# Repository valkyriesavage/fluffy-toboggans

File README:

The Fluffy Toboggans : H2O IQ

A system for watering plants remotely: you don't have to worry about them!

Final presentation of this project : https://docs.google.com/presentation/d/1S5aFqThC5lc4pM-Y68lGRSMbOaRiJMXD9njBcWfeR2Q/edit

License: GPL v3

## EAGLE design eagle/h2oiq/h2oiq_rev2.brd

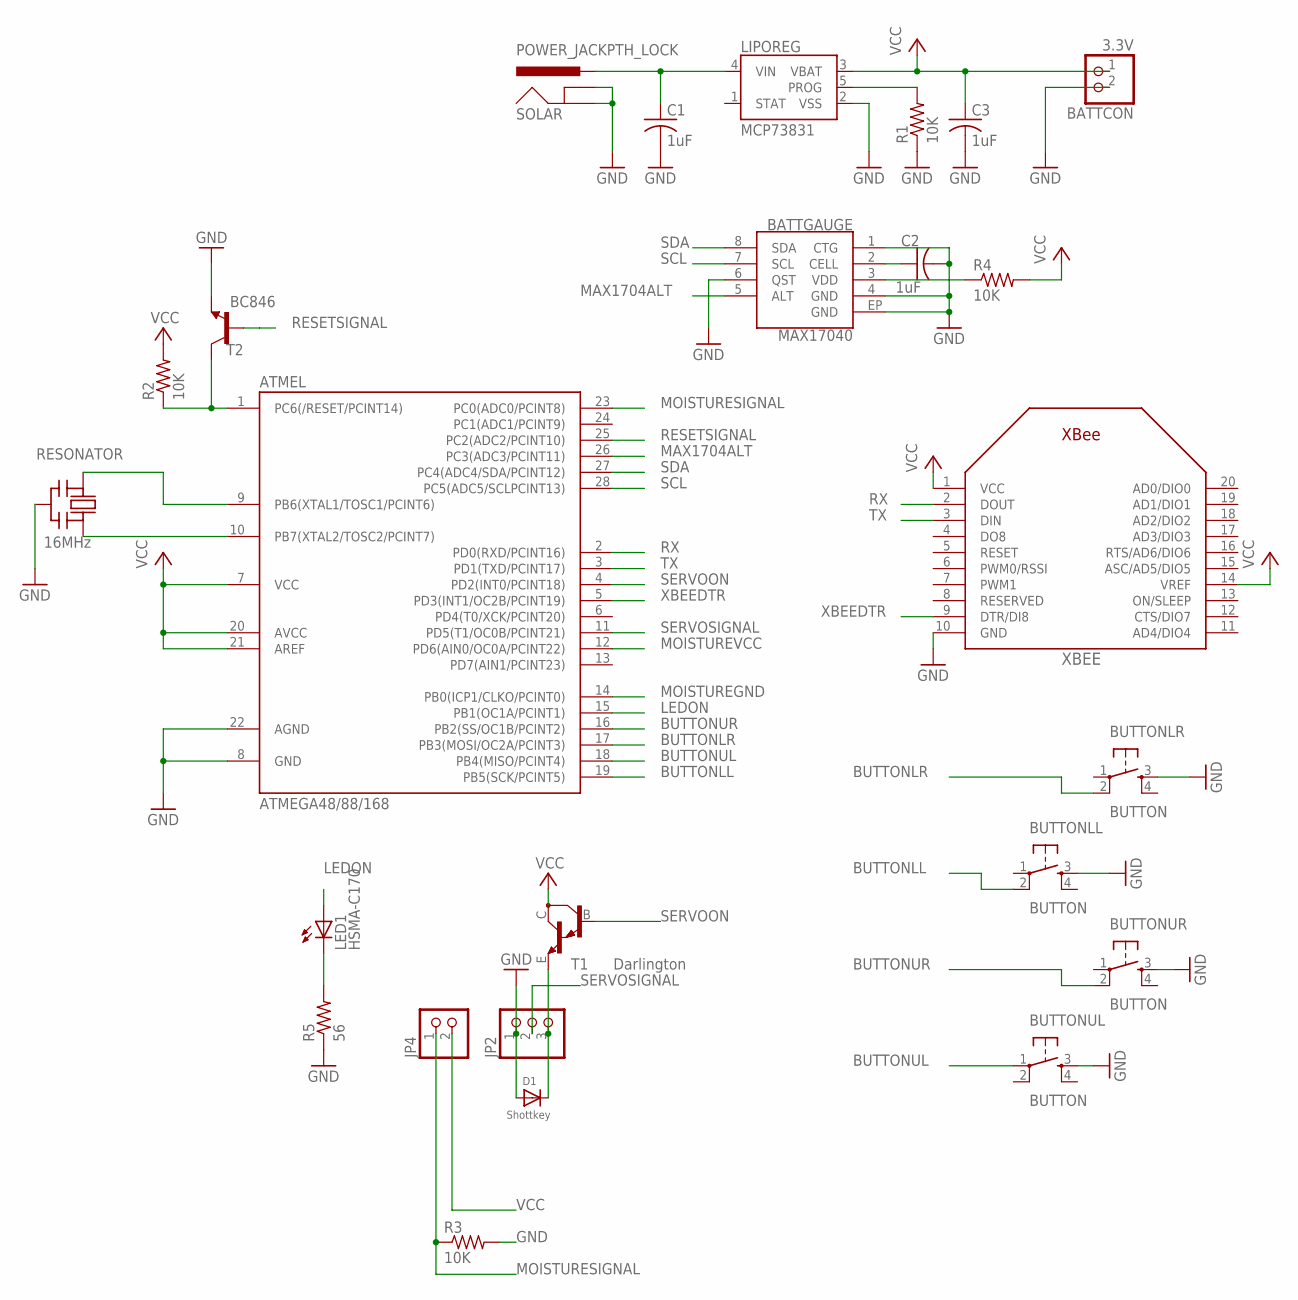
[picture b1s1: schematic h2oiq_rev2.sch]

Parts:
ATMEL: ATMEGA48/88/168; DIL28-3
BATTCON: 3.3V; JST-PH-2-THM
BATTGAUGE: MAX17040; MAX17040-TFDN
BUTTONLL: BUTTON; TACTILE-PTH
BUTTONLR: BUTTON; TACTILE-PTH
BUTTONUL: BUTTON; TACTILE-PTH
BUTTONUR: BUTTON; TACTILE-PTH
C1, C2, C3: 1uF; C0603K
D1: Shottkey; SMADIODE
JP2: PINHD-1X3; 1X03
JP4: PINHD-1X2; 1X02
LED1: HSMA-C170; LED-HSMA-SMD
LIPOREG: MCP73831; SOT23-5
R1, R2, R3, R4: 10K; R0805
R5: 56; R0805
RESONATOR: 16MHz; CERM_OSC
SOLAR: POWER_JACKPTH_LOCK; POWER_JACK_PTH_LOCK
T1: Darlington; SOT23-BEC
T2: BC846; SOT23
XBEE: XBEE

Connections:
BUTTONLL: ATMEL.19 (PB5(SCK/PCINT5)), BUTTONLL.2
BUTTONLR: ATMEL.17 (PB3(MOSI/OC2A/PCINT3)), BUTTONLR.2
BUTTONUL: ATMEL.18 (PB4(MISO/PCINT4)), BUTTONUL.1
BUTTONUR: ATMEL.16 (PB2(SS/OC1B/PCINT2)), BUTTONUR.2
GND: ATMEL.8 (GND), ATMEL.22 (AGND), BATTCON.2 (1), BATTGAUGE.1 (CTG), BATTGAUGE.4 (GND), BATTGAUGE.6 (QST), BATTGAUGE.EP (GND), BUTTONLL.3, BUTTONLR.3, BUTTONUL.3, BUTTONUR.3, C1.2, C2.2, C3.2, D1.A, JP2.1, LIPOREG.2 (VSS), R1.1, R3.2, R5.1, RESONATOR.P$2 (GND), SOLAR.GND, SOLAR.GNDBREAK, T2.2 (E), XBEE.10 (GND)
LEDON: ATMEL.15 (PB1(OC1A/PCINT1)), LED1.P$1 (A)
MAX1704ALT: ATMEL.26 (PC3(ADC3/PCINT11)), BATTGAUGE.5 (ALT)
MOISTUREGND: ATMEL.14 (PB0(ICP1/CLKO/PCINT0))
MOISTURESIGNAL: ATMEL.23 (PC0(ADC0/PCINT8)), JP4.1, R3.1
MOISTUREVCC: ATMEL.12 (PD6(AIN0/OC0A/PCINT22))
unnamed: BATTGAUGE.3 (VDD), R4.1
unnamed: LIPOREG.5 (PROG), R1.2
unnamed: ATMEL.1 (PC6(/RESET/PCINT14)), R2.1, T2.3 (C)
unnamed: ATMEL.10 (PB7(XTAL2/TOSC2/PCINT7)), RESONATOR.P$3 (OUT)
unnamed: ATMEL.9 (PB6(XTAL1/TOSC1/PCINT6)), RESONATOR.P$1 (IN)
unnamed: LED1.P$2 (C), R5.2
unnamed: BATTGAUGE.2 (CELL), C2.1
RESETSIGNAL: ATMEL.25 (PC2(ADC2/PCINT10)), T2.1 (B)
RX: ATMEL.2 (PD0(RXD/PCINT16)), XBEE.2 (DOUT)
SCL: ATMEL.28 (PC5(ADC5/SCLPCINT13)), BATTGAUGE.7 (SCL)
SDA: ATMEL.27 (PC4(ADC4/SDA/PCINT12)), BATTGAUGE.8 (SDA)
SERVOACT: D1.C, JP2.3, T1.E
SERVOON: ATMEL.4 (PD2(INT0/PCINT18)), T1.B
SERVOSIGNAL: ATMEL.11 (PD5(T1/OC0B/PCINT21)), JP2.2
TX: ATMEL.3 (PD1(TXD/PCINT17)), XBEE.3 (DIN)
VCC: ATMEL.7 (VCC), ATMEL.20 (AVCC), ATMEL.21 (AREF), BATTCON.1 (2), C3.1, JP4.2, LIPOREG.3 (VBAT), R2.2, R4.2, T1.C, XBEE.1 (VCC), XBEE.14 (VREF)
VIN: C1.1, LIPOREG.4 (VIN), SOLAR.PWR
XBEEDTR: ATMEL.5 (PD3(INT1/OC2B/PCINT19)), XBEE.9 (DTR/DI8)

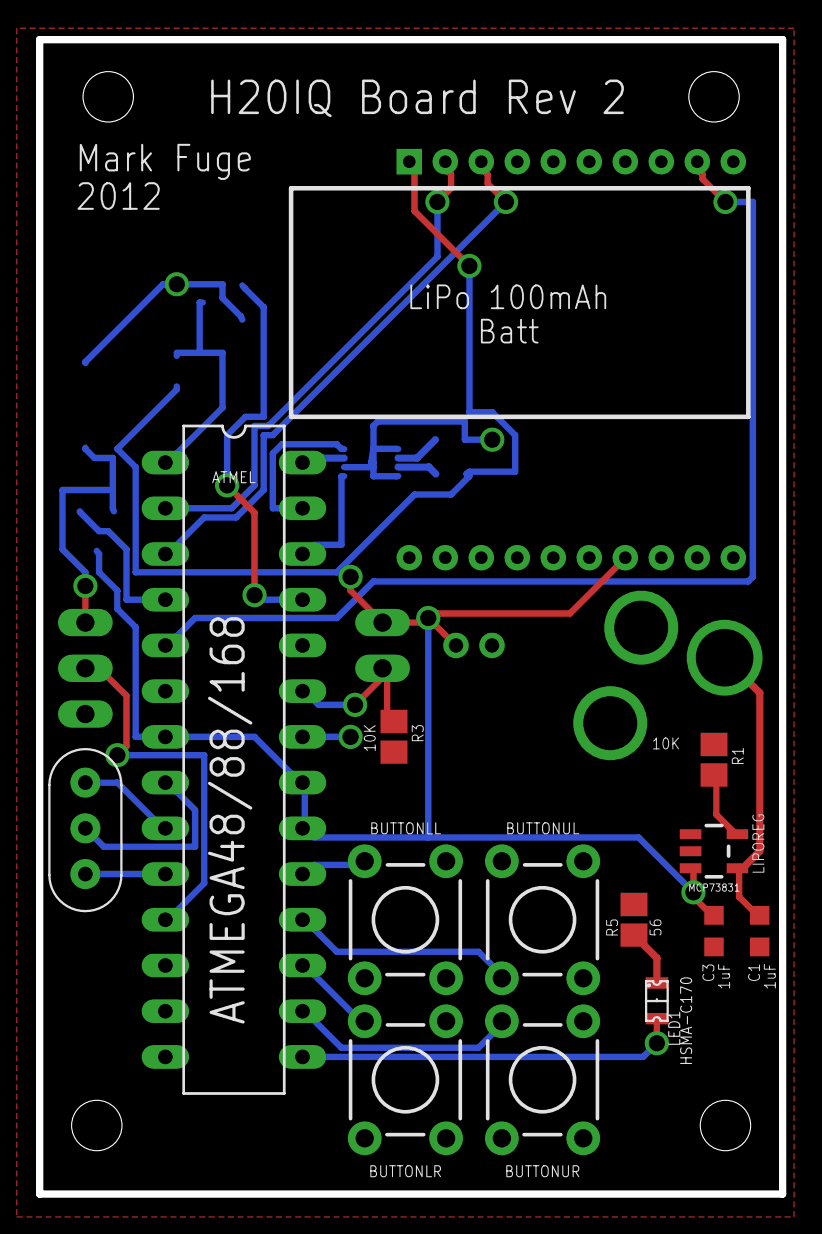
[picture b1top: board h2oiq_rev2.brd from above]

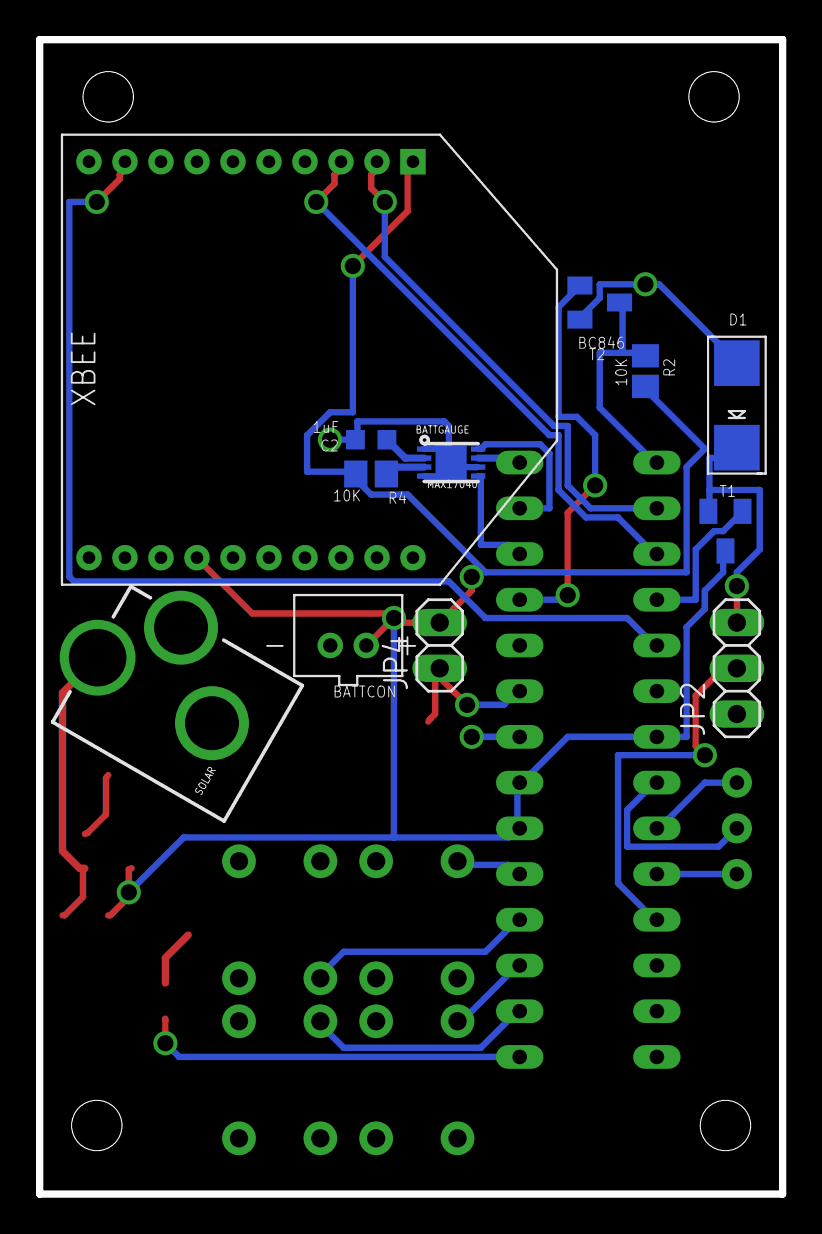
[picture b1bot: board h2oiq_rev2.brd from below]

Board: 2 copper layers, 41.3 x 64.1 mm, 25 parts (12 on the bottom side), 26 nets.

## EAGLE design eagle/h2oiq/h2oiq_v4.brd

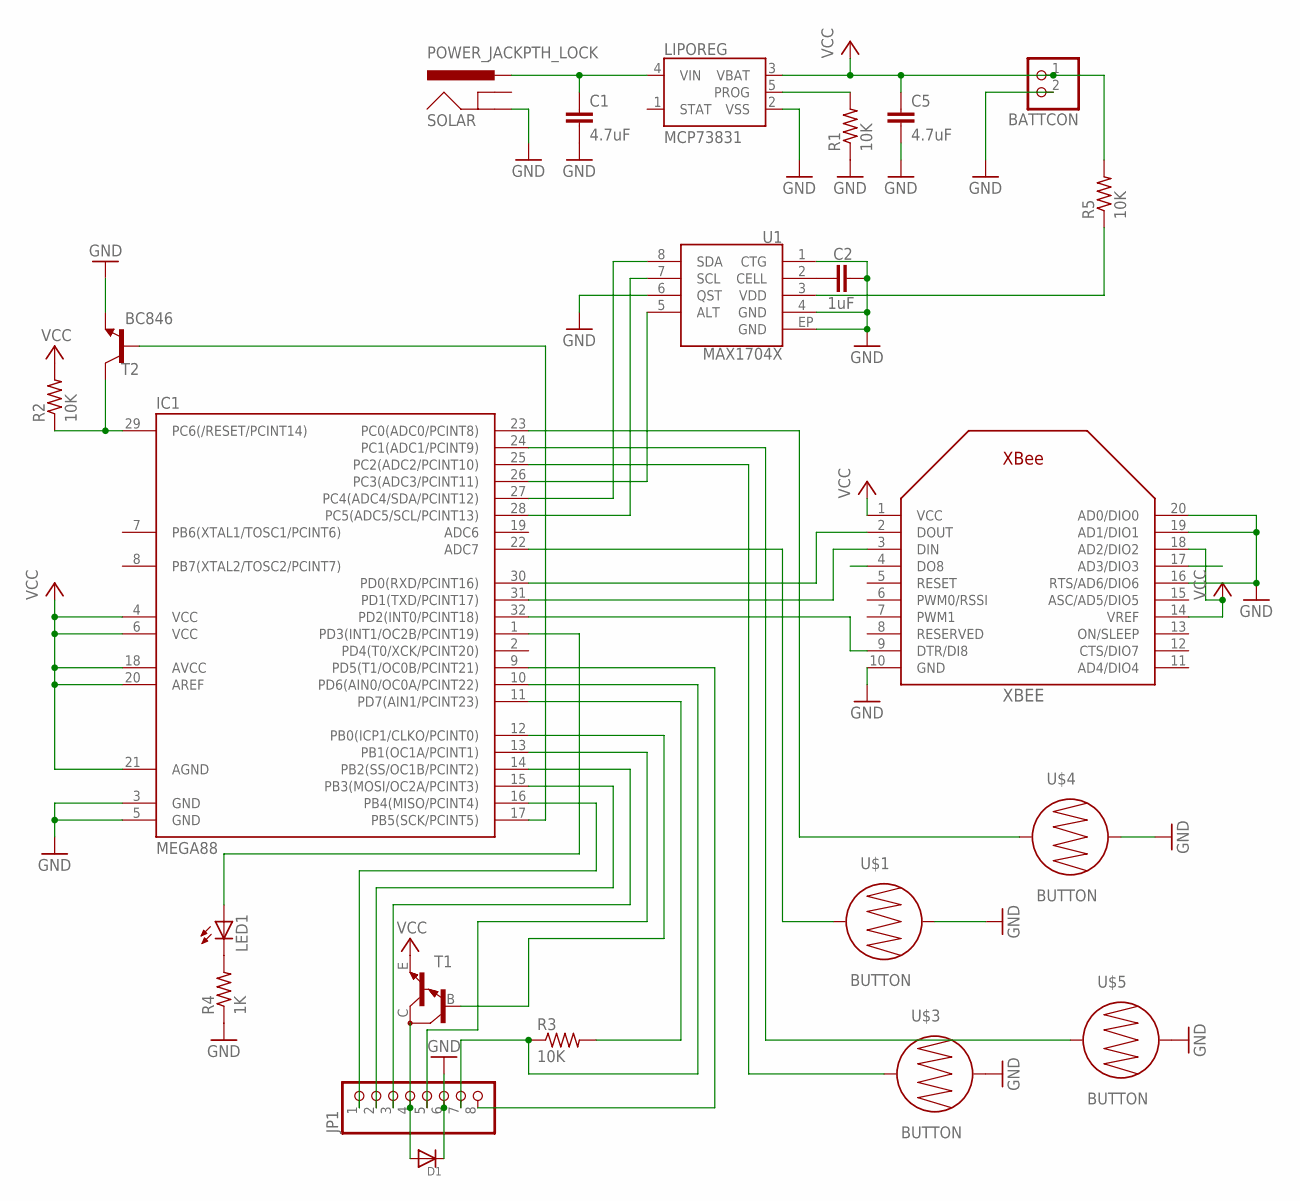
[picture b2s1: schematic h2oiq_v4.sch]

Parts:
BATTCON: JST_2PIN-SMT; JST-PH-2-SMT
C1, C5: 4.7uF; 0402-CAP
C2: 1uF; 0402-CAP
D1: DIODESMA; SMADIODE
IC1: MEGA88; MLF32
JP1: PINHD-1X8LOCK; 1X08-LOCK
LED1: LED; SMARTLED-TTW
LIPOREG: MCP73831; SOT23-5
R1, R3: 10K; R0603
R2, R5: 10K; R0603@1
R4: 1K; R0603@1
SOLAR: POWER_JACKPTH_LOCK; POWER_JACK_PTH_LOCK
T1: MMBTA13LT1-NPN_DARL-SOT23-BEC; SOT23-BEC
T2: BC846; SOT23
U1: MAX1704X; TDFN-8
U$1, U$3, U$4, U$5: BUTTON; BUTTON-CONDUCTIVE
XBEE: XBEE

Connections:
GND: BATTCON.2 (1), C1.2, C2.2, C5.2, D1.C, IC1.3 (GND), IC1.5 (GND), JP1.6, LIPOREG.2 (VSS), R1.1, R4.1, SOLAR.GND, T2.2 (E), U1.1 (CTG), U1.4 (GND), U1.6 (QST), U1.EP (GND), U$1.2, U$3.2, U$4.2, U$5.2, XBEE.10 (GND), XBEE.16 (RTS/AD6/DIO6), XBEE.19 (AD1/DIO1), XBEE.20 (AD0/DIO0)
MAX1704ALT: IC1.26 (PC3(ADC3/PCINT11)), U1.5 (ALT)
MAX1704VDD: R5.1, U1.3 (VDD), XBEE.4 (DO8)
unnamed: C1.1, LIPOREG.4 (VIN), SOLAR.PWR
unnamed: LIPOREG.5 (PROG), R1.2
unnamed: IC1.29 (PC6(/RESET/PCINT14)), R2.1, T2.3 (C)
unnamed: IC1.12 (PB0(ICP1/CLKO/PCINT0)), T1.B
unnamed: IC1.27 (PC4(ADC4/SDA/PCINT12)), U1.8 (SDA)
unnamed: IC1.28 (PC5(ADC5/SCL/PCINT13)), U1.7 (SCL)
unnamed: IC1.32 (PD2(INT0/PCINT18)), XBEE.9 (DTR/DI8)
unnamed: IC1.15 (PB3(MOSI/OC2A/PCINT3)), JP1.2
unnamed: IC1.1 (PD3(INT1/OC2B/PCINT19)), LED1.A@1 (A)
unnamed: LED1.C@1 (C), R4.2
unnamed: IC1.23 (PC0(ADC0/PCINT8)), U$4.1
unnamed: IC1.14 (PB2(SS/OC1B/PCINT2)), JP1.3
unnamed: IC1.16 (PB4(MISO/PCINT4)), JP1.1
unnamed: IC1.10 (PD6(AIN0/OC0A/PCINT22)), JP1.7, R3.1
unnamed: IC1.25 (PC2(ADC2/PCINT10)), U$3.1
unnamed: IC1.30 (PD0(RXD/PCINT16)), XBEE.2 (DOUT)
unnamed: IC1.22 (ADC7), U$1.1
unnamed: IC1.31 (PD1(TXD/PCINT17)), XBEE.3 (DIN)
unnamed: IC1.24 (PC1(ADC1/PCINT9)), U$5.1
unnamed: C2.1, U1.2 (CELL)
unnamed: IC1.13 (PB1(OC1A/PCINT1)), JP1.5
unnamed: IC1.11 (PD7(AIN1/PCINT23)), R3.2
unnamed: IC1.9 (PD5(T1/OC0B/PCINT21)), JP1.8
unnamed: IC1.17 (PB5(SCK/PCINT5)), T2.1 (B)
SERVOACT: D1.A, JP1.4, T1.C, XBEE.17 (AD3/DIO3)
VCC: BATTCON.1 (2), C5.1, IC1.4 (VCC), IC1.6 (VCC), IC1.18 (AVCC), IC1.20 (AREF), IC1.21 (AGND), LIPOREG.3 (VBAT), R2.2, R5.2, T1.E, XBEE.1 (VCC), XBEE.14 (VREF), XBEE.18 (AD2/DIO2)

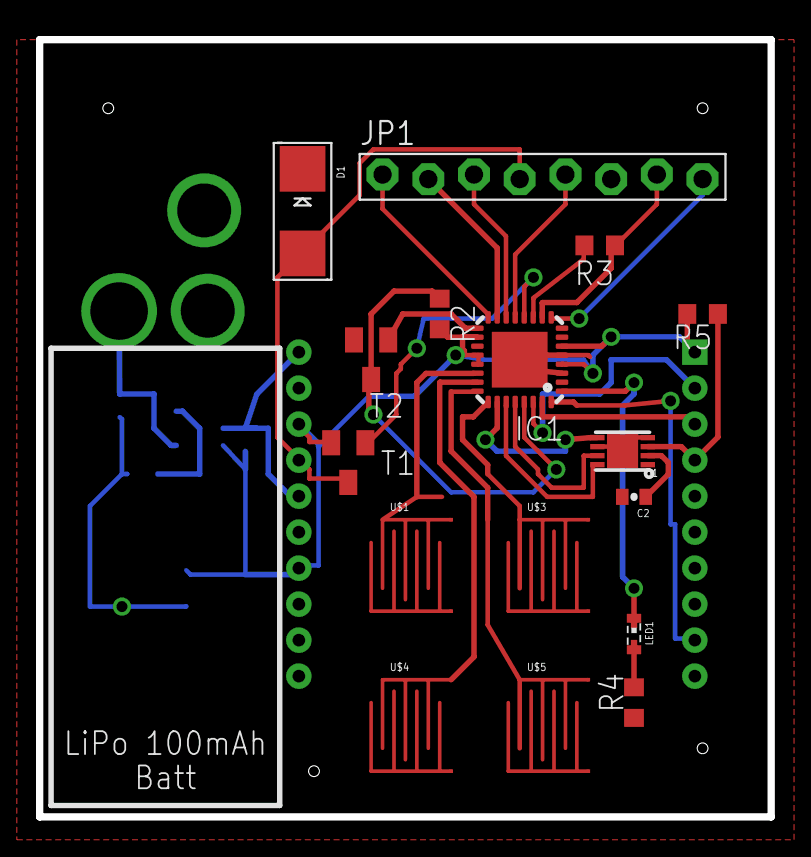
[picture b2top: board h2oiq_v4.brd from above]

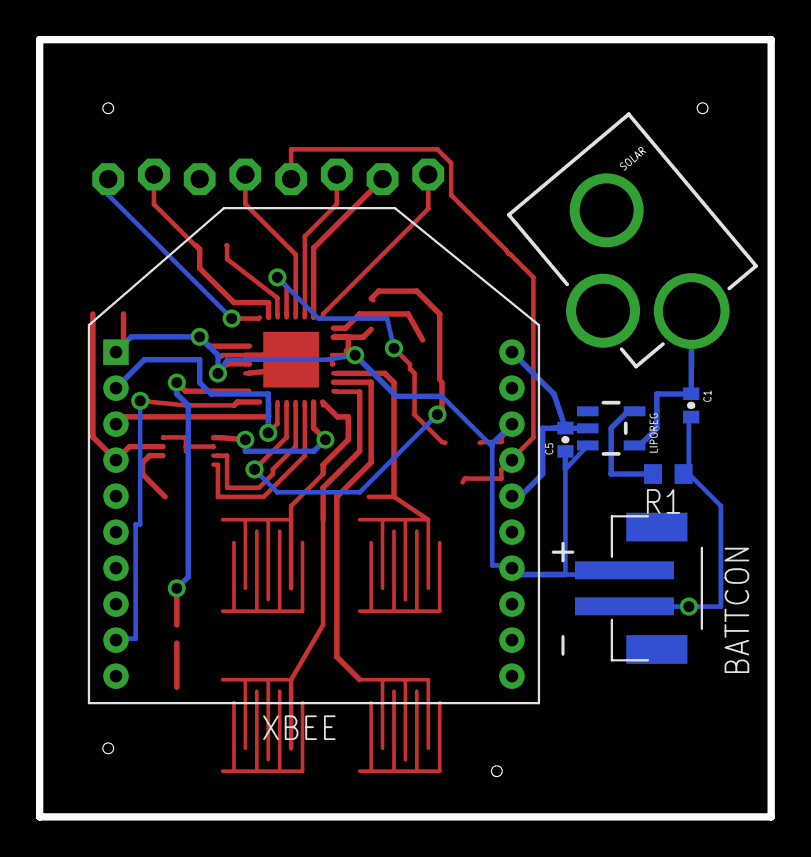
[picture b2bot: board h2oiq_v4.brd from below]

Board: 2 copper layers, 40.6 x 43.2 mm, 23 parts (7 on the bottom side), 29 nets.

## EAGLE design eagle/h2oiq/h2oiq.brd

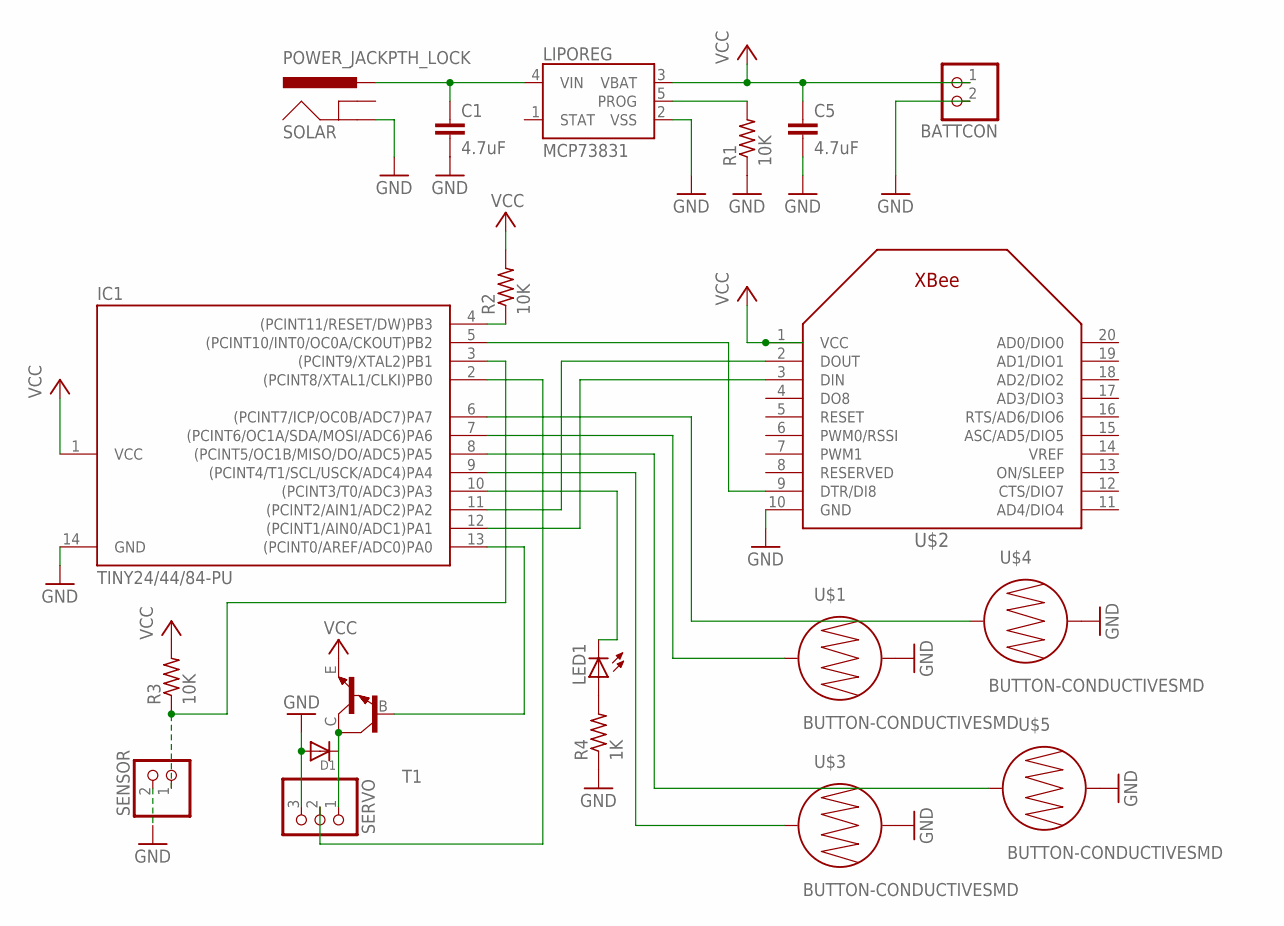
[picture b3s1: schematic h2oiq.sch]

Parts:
BATTCON: JST_2PIN-SMT; JST-PH-2-SMT
C1, C5: 4.7uF; 0402-CAP
D1: DIODESMA; SMADIODE
IC1: TINY24/44/84-PU; DIL14
LED1: LED5MM
LIPOREG: MCP73831; SOT23-5
R1, R2, R3: 10K; M1206
R4: 1K; M1206
SENSOR: JST_2PIN-SMT; JST-PH-2-SMT
SERVO: PINHD-1X3CB; 1X03-CLEANBIG
SOLAR: POWER_JACKPTH_LOCK; POWER_JACK_PTH_LOCK
T1: MMBTA13LT1-NPN_DARL-SOT23-BEC; SOT23-BEC
U$1, U$3, U$4, U$5: BUTTON-CONDUCTIVESMD; BUTTON-CONDUCTIVE
U$2: XBEE

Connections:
GND: BATTCON.2 (1), C1.2, C5.2, D1.A, IC1.14 (GND), LIPOREG.2 (VSS), R1.1, R4.1, SENSOR.2 (1), SERVO.3, SOLAR.GND, U$1.2, U$2.10 (GND), U$3.2, U$4.2, U$5.2
unnamed: C1.1, LIPOREG.4 (VIN), SOLAR.PWR
unnamed: LIPOREG.5 (PROG), R1.2
unnamed: IC1.4 ((PCINT11/RESET/DW)PB3), R2.1
unnamed: IC1.13 ((PCINT0/AREF/ADC0)PA0), T1.B
unnamed: D1.C, SERVO.1, T1.C
unnamed: IC1.5 ((PCINT10/INT0/OC0A/CKOUT)PB2), U$2.9 (DTR/DI8)
unnamed: IC1.11 ((PCINT2/AIN1/ADC2)PA2), U$2.2 (DOUT)
unnamed: IC1.12 ((PCINT1/AIN0/ADC1)PA1), U$2.3 (DIN)
unnamed: IC1.3 ((PCINT9/XTAL2)PB1), R3.1, SENSOR.1 (2)
unnamed: IC1.2 ((PCINT8/XTAL1/CLKI)PB0), SERVO.2
unnamed: LED1.A, R4.2
unnamed: IC1.10 ((PCINT3/T0/ADC3)PA3), LED1.K (C)
unnamed: IC1.7 ((PCINT6/OC1A/SDA/MOSI/ADC6)PA6), U$1.1
unnamed: IC1.6 ((PCINT7/ICP/OC0B/ADC7)PA7), U$4.1
unnamed: IC1.8 ((PCINT5/OC1B/MISO/DO/ADC5)PA5), U$5.1
unnamed: IC1.9 ((PCINT4/T1/SCL/USCK/ADC4)PA4), U$3.1
VCC: BATTCON.1 (2), C5.1, IC1.1 (VCC), LIPOREG.3 (VBAT), R2.2, R3.2, T1.E, U$2.1 (VCC)

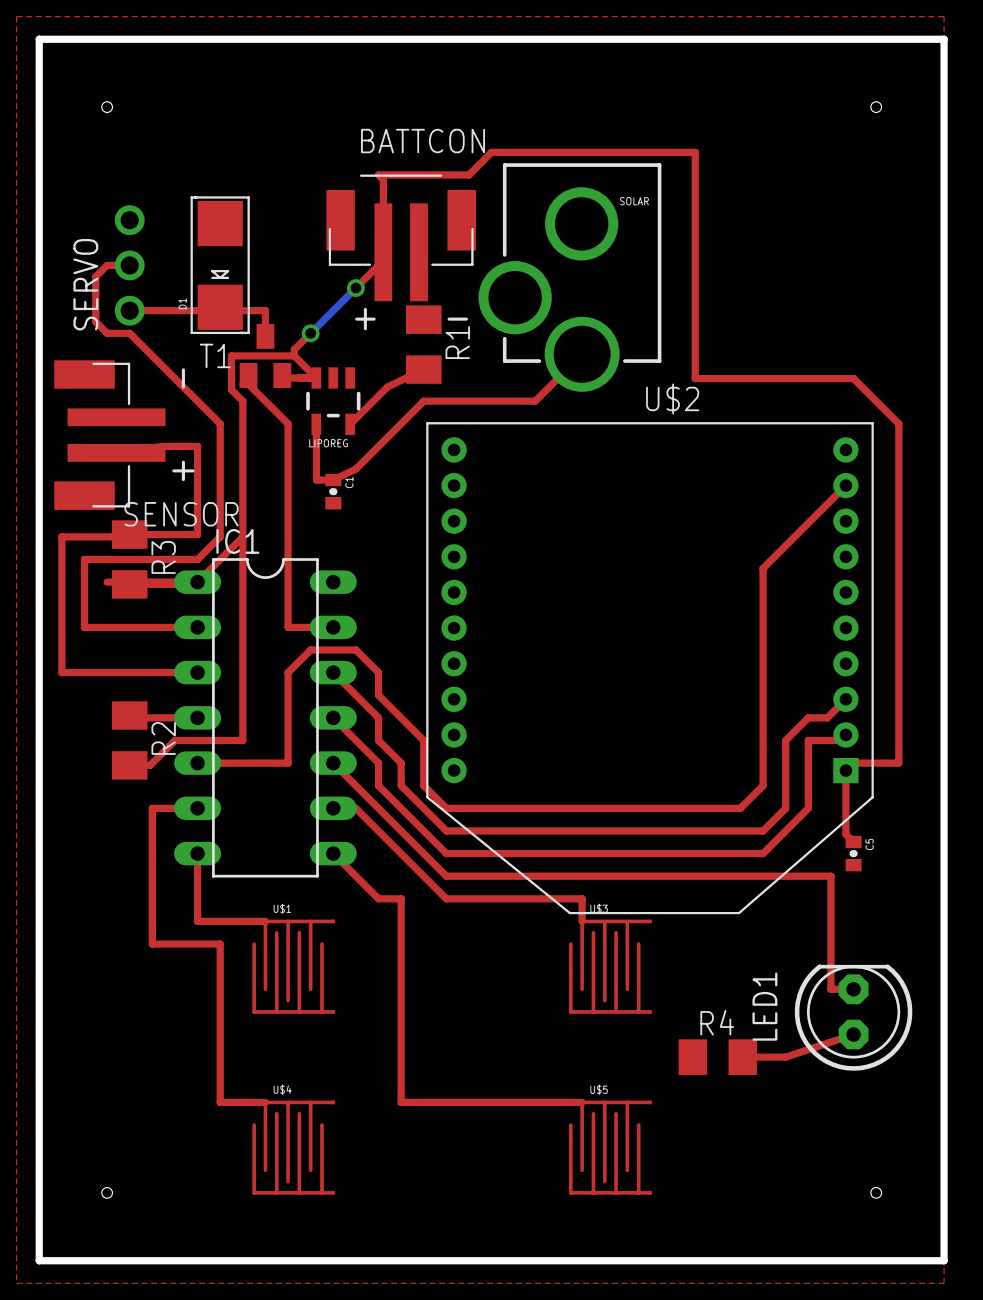
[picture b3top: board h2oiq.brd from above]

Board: 2 copper layers, 50.8 x 68.6 mm, 20 parts (0 on the bottom side), 18 nets.

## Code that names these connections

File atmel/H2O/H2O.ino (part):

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 *
 */
#include <Servo.h>
const int MOISTURE_SENSOR = A0; // PC0=A0 Signal Voltage
const int MOISTURE_VCC = 6; // PD6=D6 VCC for MoistureSensor
const int MOISTURE_GND = 8; // PB0=D8 GND for Moisture Sensor
const int MOISTURE_NONE = 550; // Analog Voltage when no water
const int MOISTURE_FULL = 650; // Analog Voltage when full water
double dmois = 50;
//const int TEMP_SENSOR = A1; // PC1=A1 Signal Voltage
//const int TEMP_VCC = 4; // PD4=D4 VCC for Temp Sensor
//const int TEMP_GND = 2; // PD2=D2 GND for Temp Sensor
//const int TEMP_0 = 54; // Analog signal when temp is 0 deg C
//const int TEMP_100 = 200; // Analog signal when temp is 100 deg C

const int CHIP_RESET = A2; // PC2=A2 Pin that resets the chip when held high.
const int XBEE_SLEEP = 3; // PD3 the pin that tells the XBEE to either wake or sleep
boolean com_success = false;

const int SERVO_SIGNAL = 5; // PD5 = D5
//TODO: Alter crystal pin to emit power as DIO
// http://arduino.cc/forum/index.php/topic,37369.0.html
const int SERVO_POWER =  2; //PB7=D21 to turn on Servo power
const int SERVO_OFF_POS = 180;
const int SERVO_ON_POS = 90;
int current_servo_pos = SERVO_OFF_POS;    // variable to store the servo position
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int current_temp = -1;

// Button Press Constants
const int LED = 9;	// PB1= D9LED for button press ack.
const int BLINK_LENGTH = 20; // In milliseconds?
// Need to add buttons here
const int BUTTON_UR = 10;	// PB2= D10 Button
const int BUTTON_LR = 11;	// PB3= D11 Button
const int BUTTON_UL = 12;	// PB4= D12 Button
const int BUTTON_LL = 13;	// PB5= D13 Button

// Battery Monitoring
const int  pSDA = A4; //PC4=A4  for two-wire signal
const int  pSCL =  A5; //PC5=A5  for two-wire clock
const int  BATT_VOLTAGE =  A3; //PC3 = A3  Battery Voltage Pin
unsigned long last_communication = 0;
unsigned long last_reading = 0;

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
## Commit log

2012-10-29 revising the device design
2012-10-30 more updates to device physical design
2012-10-30 first pass on webpage
2012-10-30 allow valve insertion
2012-10-31 finish up first round of html
2012-10-31 I hate git
2012-11-05 Adding gitignore and Eagle files
2012-11-07 New PCB board designs
2012-11-07 minor pcb change
2012-11-08 New board adjustments
2012-11-08 Adding PCB solidworks file
2012-11-08 updates to part
2012-11-08 new sexy device body
2012-11-08 version 2 of parts, ready to go but for lid adjustments
2012-11-08 updated PCB part file with XBee, Power Jack, and LED
2012-11-09 First complete revision of the H2OIQ board. Sent to OSH Park for production
2012-11-09 Finished the PCB Rev1 part
2012-11-09 yay, updates!
2012-11-10 Adding HiTec 55 servo part
2012-11-10 Adding first attempt at valve part
2012-11-12 initial thoughts on client js to work with websockets
2012-11-13 Initial shot at the SolidWorks assembly. Still need to create second valve piece for servo and to figure out valve to device attachment mechanism. Need to incorporate Valkyrie's servo mount feature i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
2012-11-14 Rev 1 of Solidworks parts and assembly. Current version would be ok for 3D printing, but not for injection molding
2012-11-15 first trial of connecting the client to the server
2012-11-15 organizing
2012-11-15 server architecture for raspberry pi
    * forked from Tinaja Labs repository, based partiall on Tornado
    example code
    * this is the basic server, nearly all functional
    * gitignore updates for pyc files
2012-11-15 Streamlining and updating
    * removing all test files we don't need
    * moved readme.md to README so it's more obvious
    * allsensors.py now does only what we need it to
    * server.py now can read sensor data files
2012-11-15 moving client code around
2012-11-15 moving more
2012-11-16 server send latest data function
    * could be improved, and we still need a notification that
    there is new data, but this is pretty good
2012-11-16 updated server and allsensors
    * now reading from log files!
    * now with data sanitation!
    * now with MOAR EXCITING
2012-11-16 making the chart draw info from the server
2012-11-16 use an array of values instead of a dict for clients
2012-11-16 chart can be drawn from server data
2012-11-16 now works with date +%s UNIX stamps
2012-11-16 now the datetime actually appears on the x axis
2012-11-17 now with timeline
2012-11-17 sending manual watering to the server
2012-11-17 now also sends instructions to the server in automatic mode
2012-11-18 XBee simplification
    * we don't need an XBee library to send strings back and forth, we
    can just write stuff and read stuff from Serial, and then
    the world is a happier place
    * instructions are now sent to a file and sent out to the XBee
    when it sends moisture readings (in JSON format)
2012-11-19 added business plan skeleton
2012-11-19 mission statement and price
2012-11-19 tasks, intended market etc
2012-11-19 ignore crap from tex generation
2012-11-19 Added tolerance adjustments for 3D printing for v2 of device
2012-11-19 Adding combined body
2012-11-20 businessplan updates
    * additional ignoring
    * more planning
    * more business
2012-11-20 fixing front end issues.
2012-11-21 Changing the lid part to deal with some 3D printer cracking issues
2012-11-21 filling in competitive landscape on business plan
2012-11-26 getting rid of mode in the title
2012-11-26 hw5 code upload for reference
2012-11-27 swapping the order of commands in auto mode
2012-11-27 protocol agreements
    * now sending chars to xbee for use at device
    * now sending newlines back in response to moisture readings
    * now touching files to make sure they exist
2012-11-27 changing more things
    * send the final command to the xbee OR send a 1
2012-11-28 Splash page
    * open splash page instead of main plant page when we are at /
    * splash page displays other plants in the garden and their
    water status
2012-11-28 testing and fixes
    * this now actually works ;)
2012-11-28 Adding LPFK board files for printing, because OSH Park completely dropped the ball on our earlier PCB order.
2012-11-28 setup guide modifications
2012-11-29 adding arduino code
2012-11-29 Minor board change for the LPFK
2012-11-30 bugfixing
2012-12-01 moar bugfixing
2012-12-01 sensor updates now show live in chart
    * removed some crufty stuff from html files
    * renamed/reworked auto water form to make sense to the server
    * fixed update function in js
    * fixed new data send function in server
2012-12-02 reverting the logic in auto mode back to what the arduino code expects - first comes the high moisture threshold, then the high one.
2012-12-02 looping through ideal moisture data
2012-12-02 display graph annotations when watering command is received
2012-12-02 fixing display issues in auto format
2012-12-03 making the data update with time and only show 30 data points at a time
2012-12-03 README update to reflect location of presentation
2012-12-03 business plan : updating, adding system arch
    * added a figure of system architecture
    * added a cost section
2012-12-03 adding images for the plant and the device
2012-12-03 adding images
2012-12-03 moved architecture image to pngs file
2012-12-04 Adding Demo Arduino Code, as well as updated board changes
2012-12-04 Adding Solidworks parts for the sensor casting assembly
2012-12-04 business plan updates : org chart, wording, figure links, cost
2012-12-04 typos
2012-12-04 business model : labor, production, overhead, design, tooling
2012-12-04 Adding Table
2012-12-04 pricing sections top
2012-12-04 more pricing
2012-12-04 deleting this pdf
2012-12-04 Adding operational costs and model spreadsheet
2012-12-04 Deleting pdf doc
2012-12-04 fixing pricing and typos
2012-12-04 fixing
2012-12-04 Final business plan
2014-05-15 Adding License Information
2014-11-13 added files in stl format

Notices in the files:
parts and their libraries:
SparkFun: Licensing: CC v3.0 Share-Alike You are welcome to use this library for commercial purposes.
